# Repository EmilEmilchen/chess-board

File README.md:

# Digital RFID-reading Chess Board

## BOMs
BOM files from suppliers are in their respective directories, DigiKey is strongly preferred, LCSC part numbers of equal or equivalent parts are given in the KiCad Symbol Table (aka. KiCad BOM) in case of using JLCPCB assembly services later.
The KiCad generated BOM file is in the root (BOM.csv).
Here is a [link to the BOM on the DigiKey website](https://www.digikey.de/de/mylists/list/6JU4LPDGX9).
Note that 4 (2x2) connectors are to be ordered from amazon or eBay since thats not only cheaper but also simpler (these are still referenced in the DigiKey BOM but not connected to any DigiKey part, same goes for the MFRC522 RFID main IC, that's about 5-10x cheaper when ordered from AliExpress (around 0.47€/pcs).
The materials in the BOM are for one sub-board (2x2 matrix of RFID readers) with a slight excess in some cases where it was cheaper to order e.g. 10 pcs instead of 8 due to bulk discounts.

### Note
The entire chess board will be made up of 16x the same 2x2 matrix circuit (around 80 USD total expected cost).

## KiCad
Use KiCad Version 10 or newer to open the .kicad_pro file, libraries are in the libs/ folder and should automatically be used.

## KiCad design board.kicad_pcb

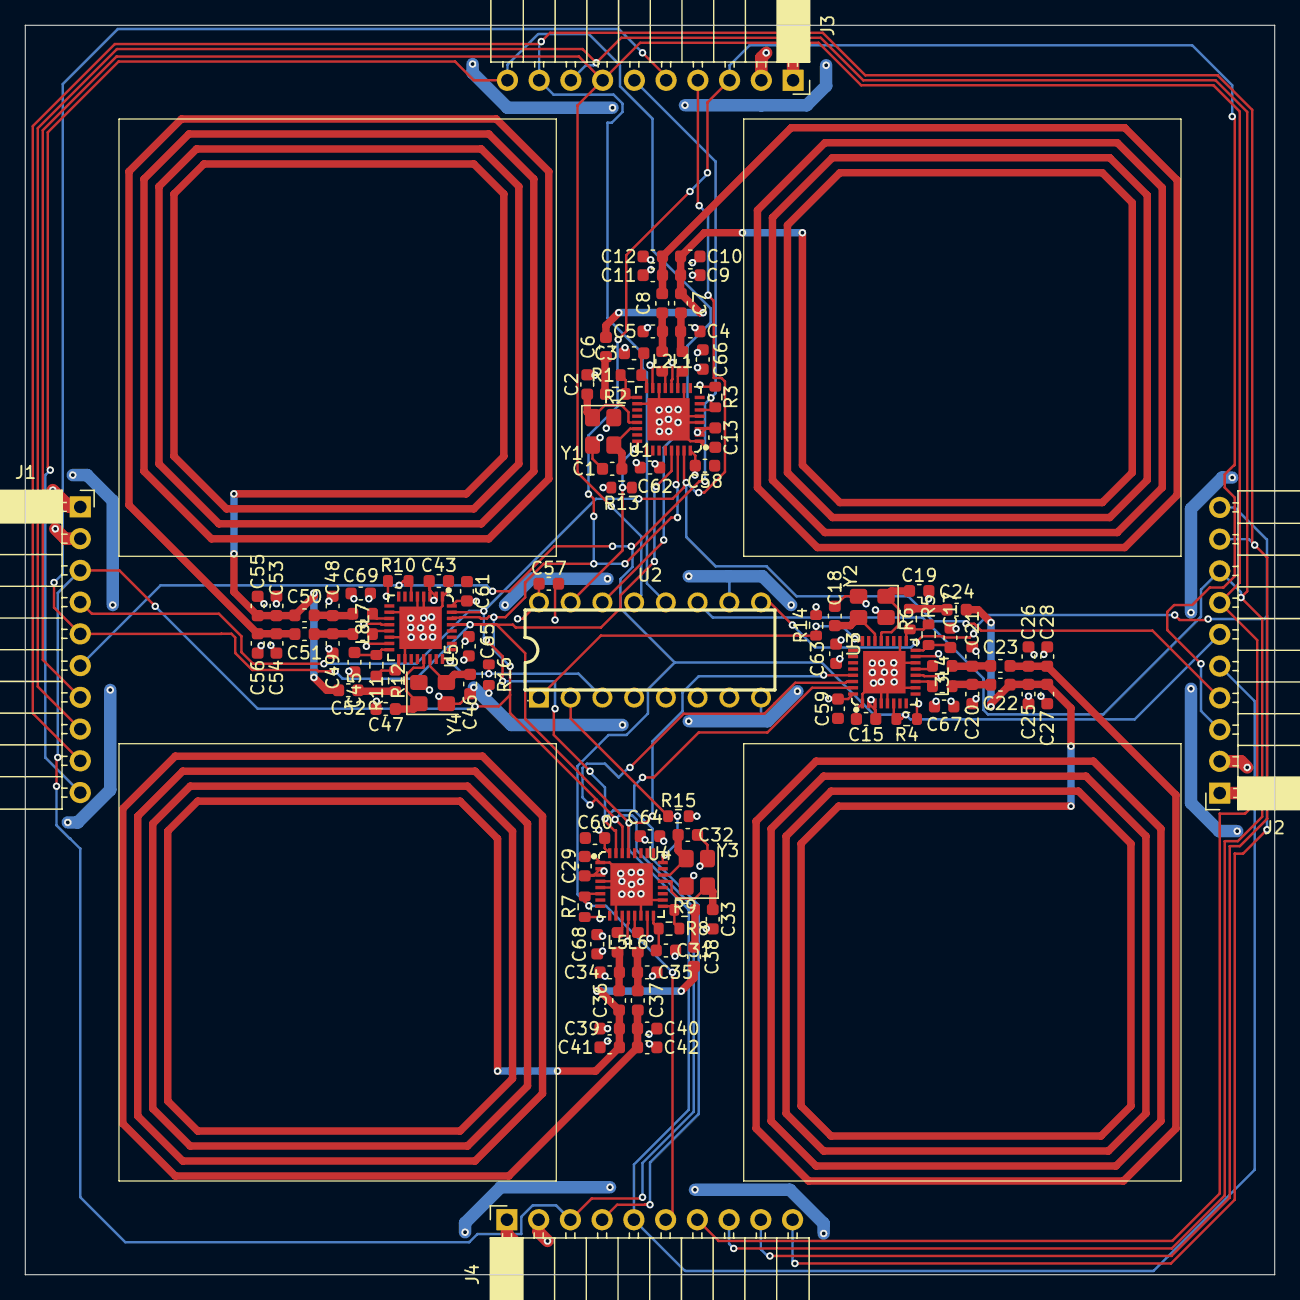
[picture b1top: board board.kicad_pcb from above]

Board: 4 copper layers, 100.0 x 100.0 mm, 102 parts (0 on the bottom side), 55 nets.

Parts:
C1, C2, C18, C19, C32, C33, C46, C47: 15pF; C_0603_1608Metric
C3, C6, C13, C15, C17, C24, C29, C31, C38, C43, C45, C52, C57, C58, C59, C60, C61, C62, C63, C64, C65: 100nF; C_0603_1608Metric
C4, C5, C20, C21, C34, C35, C48, C49: 47PF; C_0603_1608Metric
C7, C8, C22, C23, C36, C37, C50, C51: 15PF; C_0603_1608Metric
C9, C11, C25, C26, C39, C40, C53, C54: 180PF; C_0603_1608Metric
C10, C12, C27, C28, C41, C42, C55, C56: 10PF; C_0603_1608Metric
C66, C67, C68, C69: 1uF; C_0603_1608Metric
J1: IN1; PinSocket_1x10_P2.54mm_Horizontal
J2: OUT1; PinSocket_1x10_P2.54mm_Horizontal
J3: IN2; PinSocket_1x10_P2.54mm_Horizontal
J4: OUT2; PinSocket_1x10_P2.54mm_Horizontal
L1, L2, L3, L4, L5, L6, L7, L8: 2.2UH; L_0603_1608Metric
R1, R5, R8, R11: 820R; R_0603_1608Metric
R2, R6, R9, R12: 5k1; R_0603_1608Metric
R3, R4, R7, R10: 10K; R_0603_1608Metric
R13, R14, R15, R16: 10k; R_0603_1608Metric
U1, U3, U4, U5: MFRC52202HN1,151; QFN-32_L5.0-W5.0-P0.50-BL-EP3.4
U2: SN74HC595N; DIP-16_L19.8-W6.5-P2.54-LS7.6-BL
Y1, Y2, Y3, Y4: 27.12 MHz Crystal; Crystal_SMD_3225-4Pin_3.2x2.5mm

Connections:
+3V3: C13.2, C15.2, C29.2, C43.2, C57.2, C58.1, C59.1, C60.1, C61.1, C62.1, C63.1, C64.1, C65.1, C66.1, C67.1, C68.1, C69.1, J1.1, J2.1, J3.1, J4.1, R3.2, R4.2, R7.2, R10.2, R13.1, R14.1, R15.1, R16.1, U1.2 (PVDD), U1.3 (DVDD), U1.12 (TVDD), U1.15 (AVDD), U1.32 (EA), U2.10 (~SRCLR), U2.16 (VCC), U3.2 (PVDD), U3.3 (DVDD), U3.12 (TVDD), U3.15 (AVDD), U3.32 (EA), U4.2 (PVDD), U4.3 (DVDD), U4.12 (TVDD), U4.15 (AVDD), U4.32 (EA), U5.2 (PVDD), U5.3 (DVDD), U5.12 (TVDD), U5.15 (AVDD), U5.32 (EA)
/Sub Board/MISO: J1.4, J2.4, J3.4, J4.4, U1.31 (D7/SCL/MISO/TX), U3.31 (D7/SCL/MISO/TX), U4.31 (D7/SCL/MISO/TX), U5.31 (D7/SCL/MISO/TX)
/Sub Board/MOSI: J1.3, J2.3, J3.3, J4.3, U1.30 (D6/ADR_0/MOSI/MX), U3.30 (D6/ADR_0/MOSI/MX), U4.30 (D6/ADR_0/MOSI/MX), U5.30 (D6/ADR_0/MOSI/MX)
/Sub Board/OE: J1.7, J2.7, J3.7, J4.7, U2.13 (~OE)
/Sub Board/RC522-1/MFSDA-CS: R13.2, U1.24 (SDA/NSS/RX), U2.15 (QA)
/Sub Board/RC522-1/RX: R1.2, R2.1, U1.17 (RX)
/Sub Board/RC522-1/TX1: L1.1, U1.11 (TX1)
/Sub Board/RC522-1/TX2: L2.1, U1.13 (TX2)
/Sub Board/RC522-1/VMID: C3.1, R1.1, U1.16 (VMID)
/Sub Board/RC522-2/MFSDA-CS: R14.2, U2.1 (QB), U3.24 (SDA/NSS/RX)
/Sub Board/RC522-2/RX: R5.2, R6.1, U3.17 (RX)
/Sub Board/RC522-2/TX1: L3.1, U3.11 (TX1)
/Sub Board/RC522-2/TX2: L4.1, U3.13 (TX2)
/Sub Board/RC522-2/VMID: C17.1, R5.1, U3.16 (VMID)
/Sub Board/RC522-3/MFSDA-CS: R15.2, U2.2 (QC), U4.24 (SDA/NSS/RX)
/Sub Board/RC522-3/RX: R8.2, R9.1, U4.17 (RX)
/Sub Board/RC522-3/TX1: L5.1, U4.11 (TX1)
/Sub Board/RC522-3/TX2: L6.1, U4.13 (TX2)
/Sub Board/RC522-3/VMID: C31.1, R8.1, U4.16 (VMID)
/Sub Board/RC522-4/MFSDA-CS: R16.2, U2.3 (QD), U5.24 (SDA/NSS/RX)
/Sub Board/RC522-4/RX: R11.2, R12.1, U5.17 (RX)
/Sub Board/RC522-4/TX1: L7.1, U5.11 (TX1)
/Sub Board/RC522-4/TX2: L8.1, U5.13 (TX2)
/Sub Board/RC522-4/VMID: C45.1, R11.1, U5.16 (VMID)
/Sub Board/RCLK: J1.9, J2.9, J3.9, J4.9, U2.12 (RCLK)
/Sub Board/RST: J1.6, J2.6, J3.6, J4.6, R3.1, R4.1, R7.1, R10.1, U1.6 (NRSTPD), U3.6 (NRSTPD), U4.6 (NRSTPD), U5.6 (NRSTPD)
/Sub Board/SCK: J1.5, J2.5, J3.5, J4.5, U1.29 (D5/ADR_1/SCK/DTRQ), U3.29 (D5/ADR_1/SCK/DTRQ), U4.29 (D5/ADR_1/SCK/DTRQ), U5.29 (D5/ADR_1/SCK/DTRQ)
/Sub Board/SER: J1.10, J3.10, U2.14 (SER)
/Sub Board/SER_OUT: J2.10, J4.10, U2.9 (QH')
/Sub Board/SRCLK: J1.8, J2.8, J3.8, J4.8, U2.11 (SRCLK)
GND: C1.2, C2.2, C3.2, C4.2, C5.1, C9.1, C10.2, C11.2, C12.1, C13.1, C15.1, C17.2, C18.2, C19.2, C20.2, C21.1, C25.1, C26.2, C27.2, C28.1, C29.1, C31.2, C32.2, C33.2, C34.2, C35.1, C39.1, C40.2, C41.2, C42.1, C43.1, C45.2, C46.2, C47.2, C48.2, C49.1, C53.1, C54.2, C55.2, C56.1, C57.1, C58.2, C59.2, C60.2, C61.2, C62.2, C63.2, C64.2, C65.2, C66.2, C67.2, C68.2, C69.2, J1.2, J2.2, J3.2, J4.2, U1.1 (I2C), U1.4 (DVSS), U1.5 (PVSS), U1.10 (TVSS), U1.14 (TVSS), U1.18 (AVSS), U1.33 (GND), U2.8 (GND), U3.1 (I2C), U3.4 (DVSS), U3.5 (PVSS), U3.10 (TVSS), U3.14 (TVSS), U3.18 (AVSS), U3.33 (GND), U4.1 (I2C), U4.4 (DVSS), U4.5 (PVSS), U4.10 (TVSS), U4.14 (TVSS), U4.18 (AVSS), U4.33 (GND), U5.1 (I2C), U5.4 (DVSS), U5.5 (PVSS), U5.10 (TVSS), U5.14 (TVSS), U5.18 (AVSS), U5.33 (GND), Y1.2 (G), Y1.4 (G), Y2.2 (G), Y2.4 (G), Y3.2 (G), Y3.4 (G), Y4.2 (G), Y4.4 (G)
unnamed: C4.1, C7.1, L1.2
unnamed: C5.2, C8.1, L2.2
unnamed: C6.1, R2.2
unnamed: C6.2, C7.2, C8.2, C9.2, C10.1, C11.1, C12.2
unnamed: C20.1, C22.1, L3.2
unnamed: C21.2, C23.1, L4.2
unnamed: C22.2, C23.2, C24.2, C25.2, C26.1, C27.1, C28.2
unnamed: C24.1, R6.2
unnamed: C34.1, C36.1, L5.2
unnamed: C35.2, C37.1, L6.2
unnamed: C36.2, C37.2, C38.2, C39.2, C40.1, C41.1, C42.2
unnamed: C38.1, R9.2
unnamed: C48.1, C50.1, L7.2
unnamed: C49.2, C51.1, L8.2
unnamed: C50.2, C51.2, C52.2, C53.2, C54.1, C55.1, C56.2
unnamed: C52.1, R12.2
unnamed: C2.1, U1.21 (OSCIN), Y1.1
unnamed: C1.1, U1.22 (OSCOUT), Y1.3
unnamed: C19.1, U3.21 (OSCIN), Y2.1
unnamed: C18.1, U3.22 (OSCOUT), Y2.3
unnamed: C33.1, U4.21 (OSCIN), Y3.1
unnamed: C32.1, U4.22 (OSCOUT), Y3.3
unnamed: C47.1, U5.21 (OSCIN), Y4.1
unnamed: C46.1, U5.22 (OSCOUT), Y4.3

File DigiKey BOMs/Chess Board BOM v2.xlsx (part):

Das Herkunftsland kann sich zum Zeitpunkt des Versands geändert haben.
Die angezeigten HTSUS- und ECCN-Informationen dienen nur zu Informationszwecken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
Index | Hersteller-Teilenummer | Herstellername | Beschreibung | Lieferzeit | Verfügbarkeit | Lagerstatus | Verlust % | Gewünschte Menge 1 | Packungsmenge 1 | Packungstyp 1 | Digi-Key-Teilenr. 1 | Stückpreis 1 | Gesamtpreis 1 | Mindestbestellmenge 1 | Kundenreferenz | Gewünschte Teilenummer | Lieferzeit in Wochen | Datenblatt | Referenzbezeichner | US-Einfuhrzoll | Hinweis | Status der Komponente | RoHS-Status | REACH-Status | Feuchteempfindlichkeit (MSL) | ECCN | HTSUS | Herkunftsland | Informationen zur Umweltverträglichkeit | Original-Teilenummern | Maßeinheit | Abbildung | Produkthinweise
1 | CL10C150JB8NNNC | Samsung Electro-Mechanics | CAP CER 15PF 50V C0G/NP0 0603 |  | 58.491 | Artikel auf Lager |  | 16 | 16 | Cut Tape (CT) | 1276-1296-1-ND | 0,03800 | 0,61 $ | 1 | 15pF NP0 | 1276-1296-2-ND | 31 | https://weblib.samsungsem.com/mlcc/mlcc-ec-data-sheet.do?par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 | C1,C2,C7,C8,C18,C19,C22,C23,C32,C33,C36,C37,C46,C47,C50,C51 | N/A |  | Aktiv | RoHS3-konform | Von REACH nicht betroffen | 1 (Unbegrenzt) | EAR99 | 8532.24.0020 | Philippines | https://www.samsungsem.com/files/fileDown.do?key=ed1dfdfa-64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 | 1276-1296-2-ND | Each | https://mm.digikey.com/Volume0/opasdata/d220001/medias/image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
2 | CL10B104KB8NNNC | Samsung Electro-Mechanics | CAP CER 0.1UF 50V X7R 0603 |  | 6.517.749 | Artikel auf Lager |  | 21 | 21 | Cut Tape (CT) | 1276-1000-1-ND | 0,02700 | 0,57 $ | 1 | 100nF | 1276-1000-2-ND | 31 | https://mm.digikey.com/Volume0/opasdata/d220001/medias/docus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 | C3,C6,C13,C15,C17,C24,C29,C31,C38,C43,C45,C52,C57,C58,C59,C60,C61,C62,C63,C64,C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 | N/A |  | Aktiv | RoHS3-konform | Von REACH nicht betroffen | 1 (Unbegrenzt) | EAR99 | 8532.24.0020 | Philippines | https://www.samsungsem.com/files/fileDown.do?key=ed1dfdfa-64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 | 1276-1000-2-ND | Each | https://mm.digikey.com/Volume0/opasdata/d220001/medias/image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
3 | CL10C470JB8NNNC | Samsung Electro-Mechanics | CAP CER 47PF 50V C0G/NP0 0603 |  | 1.515.314 | Artikel auf Lager |  | 10 | 10 | Cut Tape (CT) | 1276-1037-1-ND | 0,03600 | 0,36 $ | 1 | 47pF NP0 | 1276-1037-2-ND | 31 | https://mm.digikey.com/Volume0/opasdata/d220001/medias/docus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 | C4,C5,C20,C21,C34,C35,C48,C49 | N/A |  | Aktiv | RoHS3-konform | Von REACH nicht betroffen | 1 (Unbegrenzt) | EAR99 | 8532.24.0020 | China | https://www.samsungsem.com/files/fileDown.do?key=ed1dfdfa-64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 | 1276-1037-2-ND | Each | https://mm.digikey.com/Volume0/opasdata/d220001/medias/image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
4 | GRM1885C1H181JA01D | Murata Electronics | CAP CER 180PF 50V C0G/NP0 0603 |  | 33.152 | Artikel auf Lager |  | 10 | 10 | Cut Tape (CT) | 490-1433-1-ND | 0,07700 | 0,77 $ | 1 | 180pF NP0 | 490-1433-2-ND | 17 | https://search.murata.co.jp/Ceramy/image/img/A01X/G101/ENG/G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 | C9,C11,C25,C26,C39,C40,C53,C54 | N/A |  | Nicht für neue Designs | RoHS3-konform | Von REACH nicht betroffen | 1 (Unbegrenzt) | EAR99 | 8532.24.0020 | Japan |  | 490-1433-2-ND | Each | https://mm.digikey.com/Volume0/opasdata/d220001/medias/image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
5 | CL10C100JB8NNNC | Samsung Electro-Mechanics | CAP CER 10PF 50V C0G/NP0 0603 |  | 216.308 | Artikel auf Lager |  | 10 | 10 | Cut Tape (CT) | 1276-1027-1-ND | 0,03100 | 0,31 $ | 1 | 10pF NP0 | 1276-1027-2-ND | 31 | https://mm.digikey.com/Volume0/opasdata/d220001/medias/docus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 | C10,C12,C27,C28,C41,C42,C55,C56 | N/A |  | Aktiv | RoHS3-konform | Von REACH nicht betroffen | 1 (Unbegrenzt) | EAR99 | 8532.24.0020 | Philippines | https://www.samsungsem.com/files/fileDown.do?key=ed1dfdfa-64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 | 1276-1027-2-ND | Each | https://mm.digikey.com/Volume0/opasdata/d220001/medias/image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
6 | CL10A105KB8NNNC | Samsung Electro-Mechanics | CAP CER 1UF 50V X5R 0603 |  | 1.684.864 | Artikel auf Lager |  | 4 | 4 | Cut Tape (CT) | 1276-1860-1-ND | 0,11000 | 0,44 $ | 1 | 1uF | 1276-1860-2-ND | 31 | https://mm.digikey.com/Volume0/opasdata/d220001/medias/docus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 | C66,C67,C68,C69 | N/A |  | Aktiv | RoHS3-konform | Von REACH nicht betroffen | 1 (Unbegrenzt) | EAR99 | 8532.24.0020 | Philippines | https://www.samsungsem.com/files/fileDown.do?key=ed1dfdfa-64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 | 1276-1860-2-ND | Each | https://mm.digikey.com/Volume0/opasdata/d220001/medias/image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
7 | MLZ1608N2R2LT000 | TDK | FIXED IND 2.2UH 500MA 180 MOHM |  | 35.693 | Artikel auf Lager |  | 10 | 10 | Cut Tape (CT) | 445-6754-1-ND | 0,08800 | 0,88 $ | 1 | 2.2UH | 445-6754-2-ND | 15 | https://product.tdk.com/en/system/files?file=dam/doc/product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 | L1,L2,L3,L4,L5,L6,L7,L8 | N/A |  | Aktiv | RoHS3-konform | Von REACH nicht betroffen | 1 (Unbegrenzt) | EAR99 | 8504.50.4000 | Japan | https://product.tdk.com/en/environment/index.html | 445-6754-2-ND | Each | https://mm.digikey.com/Volume0/opasdata/d220001/medias/image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
8 | RC0603FR-07820RL | YAGEO | RES 820 OHM 1% 1/10W 0603 |  | 14 | Artikel auf Lager |  | 10 | 10 | Cut Tape (CT) | 311-820HRCT-ND | 0,02500 | 0,25 $ | 1 | 820R | 311-820HRTR-ND | 17 | https://yageogroup.com/content/datasheet/asset/file/PYU-RC_G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 | R1,R5,R8,R11 | N/A |  | Aktiv | RoHS3-konform | Von REACH nicht betroffen | 1 (Unbegrenzt) | EAR99 | 8533.21.0030 | Taiwan | https://www.yageogroup.com/content/Resource%20Library/Produc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 | 311-820HRTR-ND | Each | https://mm.digikey.com/Volume0/opasdata/d220001/derivates/6/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
9 | RC0603FR-075K1L | YAGEO | RES 5.1K OHM 1% 1/10W 0603 |  | 746.977 | Artikel auf Lager |  | 10 | 10 | Cut Tape (CT) | 311-5.10KHRCT-ND | 0,02500 | 0,25 $ | 1 | 5k1 | 311-5.10KHRTR-ND | 17 | https://yageogroup.com/content/datasheet/asset/file/PYU-RC_G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 | R2,R6,R9,R12 | N/A |  | Aktiv | RoHS3-konform | Von REACH nicht betroffen | 1 (Unbegrenzt) | EAR99 | 8533.21.0030 | Taiwan | https://www.yageogroup.com/content/Resource%20Library/Produc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 | 311-5.10KHRTR-ND | Each | https://mm.digikey.com/Volume0/opasdata/d220001/derivates/6/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
10 | RC0603FR-0710KL | YAGEO | RES 10K OHM 1% 1/10W 0603 |  | 11.782.808 | Artikel auf Lager |  | 10 | 10 | Cut Tape (CT) | 311-10.0KHRCT-ND | 0,02500 | 0,25 $ | 1 | 10k | 311-10.0KHRTR-ND | 17 | https://yageogroup.com/content/datasheet/asset/file/PYU-RC_G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 | R3,R4,R7,R10,R13,R14,R15,R16 | N/A |  | Aktiv | RoHS3-konform | Von REACH nicht betroffen | 1 (Unbegrenzt) | EAR99 | 8533.21.0030 | Taiwan | https://www.yageogroup.com/content/Resource%20Library/Produc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 | 311-10.0KHRTR-ND | Each | https://mm.digikey.com/Volume0/opasdata/d220001/derivates/6/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
11 | SN74HC595N | Texas Instruments | IC SR TRI-STATE 8BIT 16-PDIP |  | 4.821 | Artikel auf Lager |  | 1 | 1 | Tube | 296-1600-5-ND | 1,79000 | 1,79 $ | 1 | SN74HC595N | 296-1600-5-ND | 6 | https://www.ti.com/general/docs/suppproductinfo.tsp?distId=1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 | U2 | N/A |  | Aktiv | RoHS3-konform | Von REACH nicht betroffen | Nicht anwendbar | EAR99 | 8542.39.0070 | United States |  | 296-1600-5-ND | Each | https://mm.digikey.com/Volume0/opasdata/d220001/medias/image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
12 | RH100-27.120-10-F-1010-TR | Raltron Electronics | CRYSTAL 27.1200MHZ 10PF SMD |  | 1.176 | Artikel auf Lager |  | 4 | 4 | Cut Tape (CT) | 2151-RH100-27.120-10-F-1010-TRCT-ND | 0,18000 | 0,72 $ | 1 | 27.12 MHz Crystal | 2151-RH100-27.120-10-F-1010-TR-ND | 12 | https://www.raltron.com/webproducts/specs/CRYSTAL/RH100-27.1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 | Y1,Y2,Y3,Y4 | N/A |  | Aktiv | RoHS3-konform | Von REACH nicht betroffen | 1 (Unbegrenzt) | EAR99 | 8541.60.0060 | China | https://www.raltron.com/webproducts/technical/REACH.pdf|https://www.raltron.com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 | 2151-RH100-27.120-10-F-1010-TR-ND | Each | https://mm.digikey.com/Volume0/opasdata/d220001/derivates/6/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
13 |  |  |  |  |  |  |  | 4 |  |  |  |  |  |  | MFRC52202HN1,151 | MFRC52202HN1,151-AliExpress | N/A |  | U1,U3,U4,U5 |  | from AliExpress (way cheaper) |  | - | - |  | - | - | - |  | MFRC52202HN1,151-AliExpress |  |  | Für diesen Eintrag kann kein Angebot erstellt werden, da das Produkt nicht von 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

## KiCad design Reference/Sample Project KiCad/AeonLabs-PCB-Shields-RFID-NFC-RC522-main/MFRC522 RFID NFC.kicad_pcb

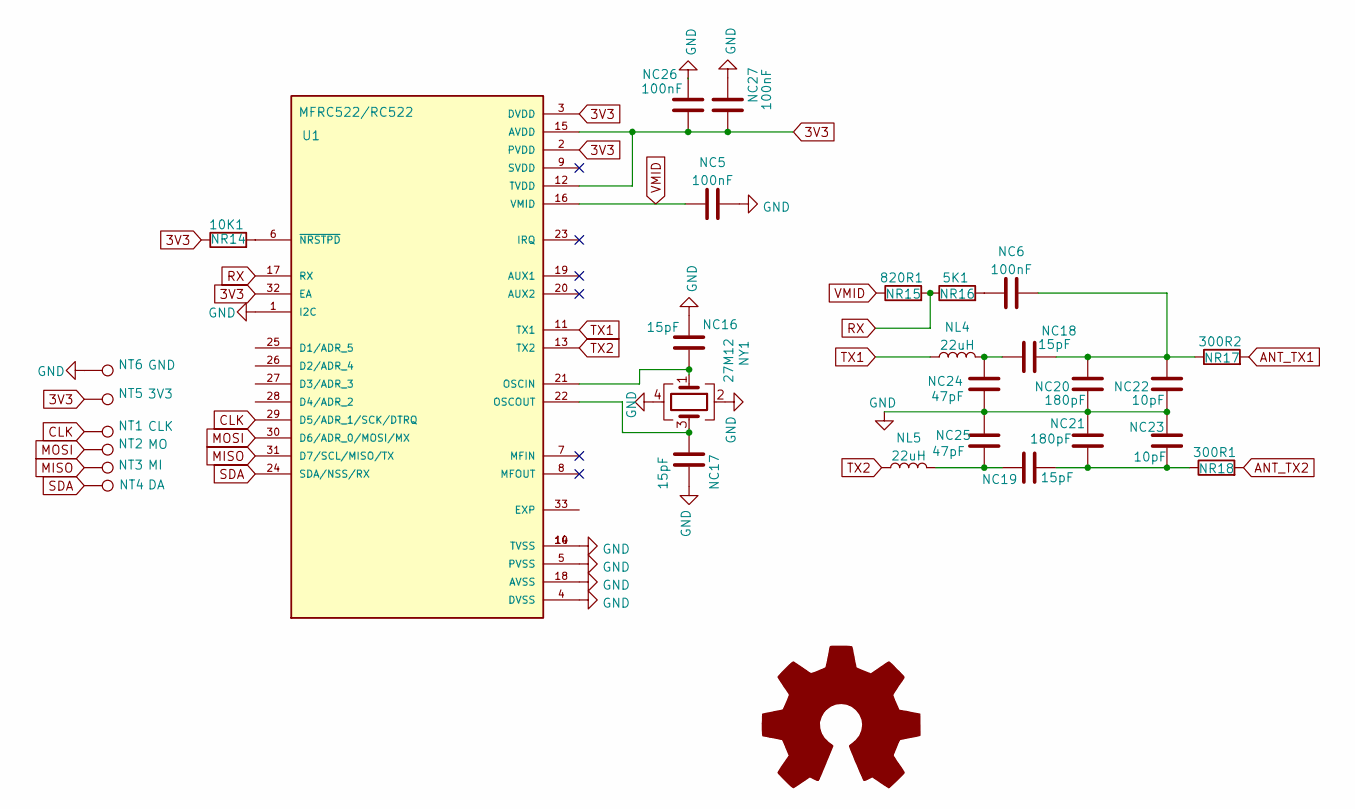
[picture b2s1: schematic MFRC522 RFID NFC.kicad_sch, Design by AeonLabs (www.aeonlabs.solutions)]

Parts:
5K1: NR16; R_0805_2012Metric_Pad1.20x1.40mm_HandSolder
10K1: NR14; R_0805_2012Metric_Pad1.20x1.40mm_HandSolder
300R1: NR18; R_0805_2012Metric_Pad1.20x1.40mm_HandSolder
300R2: NR17; R_0805_2012Metric_Pad1.20x1.40mm_HandSolder
820R1: NR15; R_0805_2012Metric_Pad1.20x1.40mm_HandSolder
NC5, NC6, NC26, NC27: 100nF; C_0805_2012Metric_Pad1.18x1.45mm_HandSolder
NC16, NC17, NC18, NC19: 15pF; C_0805_2012Metric_Pad1.18x1.45mm_HandSolder
NC20, NC21: 180pF; C_0805_2012Metric_Pad1.18x1.45mm_HandSolder
NC22, NC23: 10pF; C_0805_2012Metric_Pad1.18x1.45mm_HandSolder
NC24, NC25: 47pF; C_0805_2012Metric_Pad1.18x1.45mm_HandSolder
NL4, NL5: 22uH; L_0805_2012Metric_Pad1.15x1.40mm_HandSolder
NT1: CLK; TestPoint_Pad_1.0x1.0mm
NT2: MO; TestPoint_Pad_1.0x1.0mm
NT3: MI; TestPoint_Pad_1.0x1.0mm
NT4: DA; TestPoint_Pad_1.0x1.0mm
NT5: 3V3; TestPoint_Pad_1.0x1.0mm
NT6: GND; TestPoint_Pad_1.0x1.0mm
NY1: 27M12; Crystal_SMD_3225-4Pin_3.2x2.5mm_HandSoldering
U1: MFRC522/RC522; RC522 RFID NFC QFN50P500X500X100-33N; PARTREV 3.9

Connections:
3V3: 10K1.1, NC26.1, NC27.1, NT5.1, U1.2 (PVDD), U1.3 (DVDD), U1.12 (TVDD), U1.15 (AVDD), U1.32 (EA)
ANT_TX1: 300R2.2
ANT_TX2: 300R1.2
CLK: NT1.1, U1.29 (D5/ADR_1/SCK/DTRQ)
GND: NC5.2, NC16.2, NC17.2, NC20.2, NC21.1, NC22.2, NC23.1, NC24.2, NC25.1, NC26.2, NC27.2, NT6.1, NY1.2, NY1.4, U1.1 (I2C), U1.4 (DVSS), U1.5 (PVSS), U1.10 (TVSS), U1.14 (TVSS), U1.18 (AVSS)
MISO: NT3.1, U1.31 (D7/SCL/MISO/TX)
MOSI: NT2.1, U1.30 (D6/ADR_0/MOSI/MX)
unnamed: 5K1.2, NC6.1
unnamed: 10K1.2, U1.6 (~NRSTPD)
unnamed: NC16.1, NY1.1, U1.21 (OSCIN)
unnamed: NC17.1, NY1.3, U1.22 (OSCOUT)
unnamed: NC18.1, NC24.1, NL4.2
unnamed: 300R2.1, NC6.2, NC18.2, NC20.1, NC22.1
unnamed: NC19.1, NC25.2, NL5.2
unnamed: 300R1.1, NC19.2, NC21.2, NC23.2
RX: 5K1.1, 820R1.2, U1.17 (RX)
SDA: NT4.1, U1.24 (SDA/NSS/RX)
TX1: NL4.1, U1.11 (TX1)
TX2: NL5.1, U1.13 (TX2)
VMID: 820R1.1, NC5.1, U1.16 (VMID)

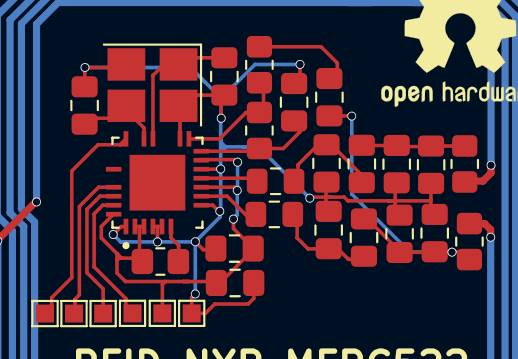
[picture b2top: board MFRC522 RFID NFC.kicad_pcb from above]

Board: 2 copper layers, 29 parts (0 on the bottom side), 18 nets.

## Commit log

2026-06-10 project innit
2026-06-10 schematics inital complete
2026-06-11 PCB: one layout done, trying replication now
2026-06-12 Previous stuff and im now at a point where a single reader circuit should be ready for replecation
2026-06-12 Added non replication-relevant traces and keepout zones
2026-06-12 Replacted layout and places replicas
2026-06-12 added all routing (very, very ugly but theoretically done)
2026-06-18 not sure what changed actually
2026-06-18 added BOM
2026-06-19 Revise README with project title and BOM details
    Updated project title and added detailed BOM information.
2026-06-19 Update pricing information for connectors and IC
2026-06-19 Add BOMs and KiCad sections to README
    Added sections for BOMs and KiCad usage instructions.
2026-06-19 Update chessboard PCB layout
2026-06-19 added BOMs and Plot
2026-06-19 Update README with BOM information and links
    Added link to DigiKey BOM and clarified BOM details.
2026-06-20 changed pcb view settings
2026-06-29 Add note about chess board assembly and cost
    Added a note about the chess board's structure and cost.
